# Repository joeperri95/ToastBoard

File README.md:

# ToastBoard

Why use a breadboard when all your I/O is right here?

## Features

* 4 LEDs
* 4 Push buttons
* Quad DIP switch
* 2 Potentiometers
* I2C EEPROM
* I2C temperature sensor

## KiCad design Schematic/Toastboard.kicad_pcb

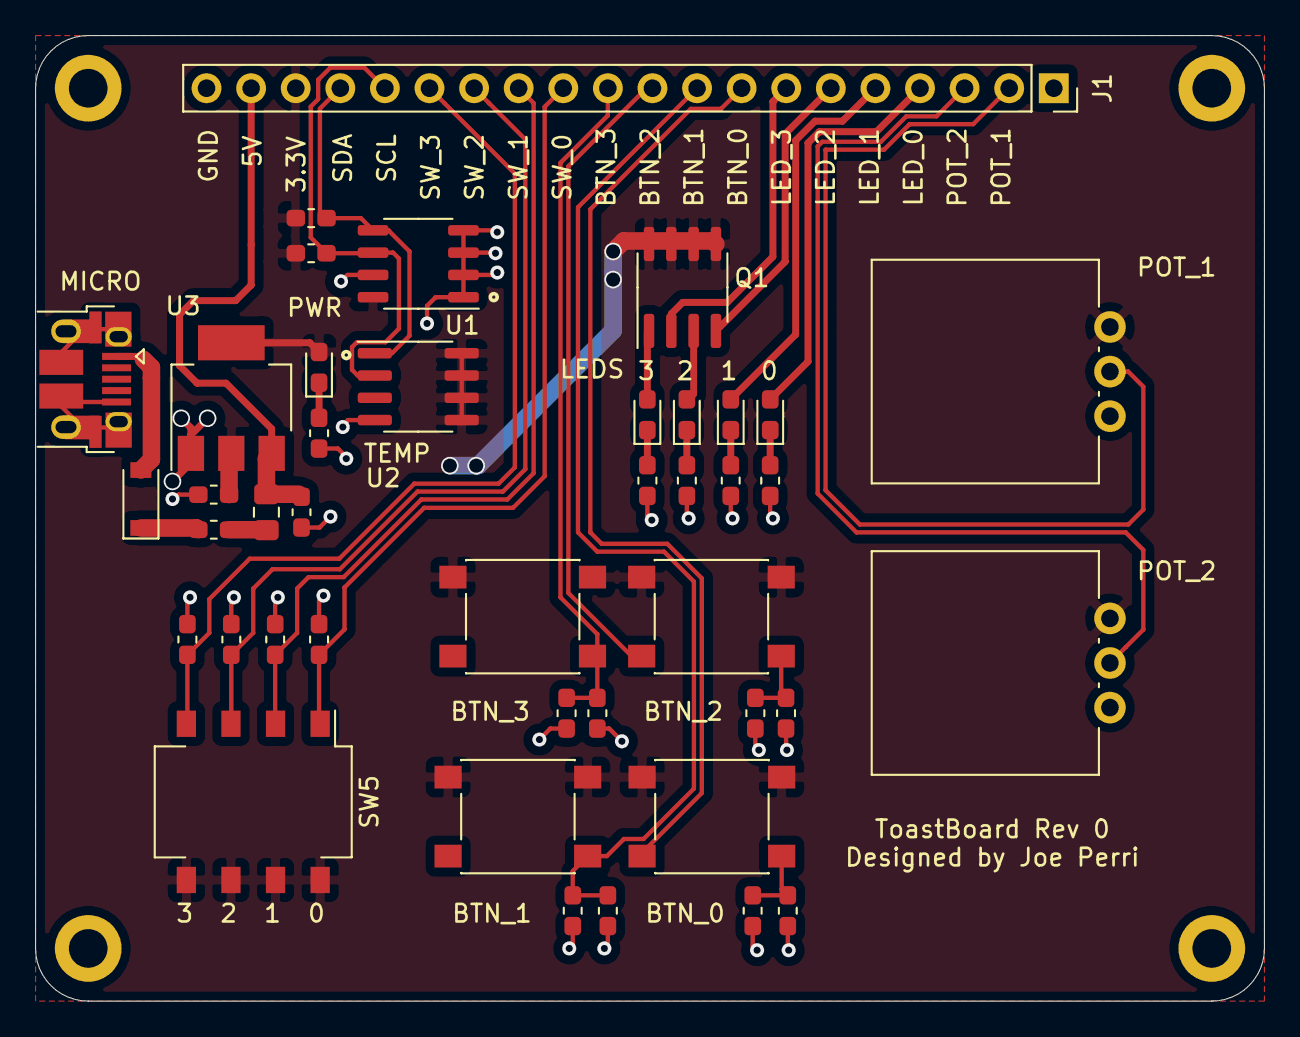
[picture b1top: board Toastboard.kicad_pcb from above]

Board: 2 copper layers, 70.0 x 55.0 mm, 46 parts (0 on the bottom side), 29 nets.

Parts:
BTN_0, BTN_1, BTN_2, BTN_3: SW_Push; SW_Push_1P1T_NO_6x6mm_H9.5mm
C1, C2: 10u; C_0603_1608Metric_Pad1.05x0.95mm_HandSolder
C3, C4, C5, C6: 100n; C_0603_1608Metric_Pad1.05x0.95mm_HandSolder
D1, D3, D4, D5, D6: LED; LED_0603_1608Metric_Pad1.05x0.95mm_HandSolder
D2: D_Schottky; D_SOD-123
F1: 1A; Fuse_0603_1608Metric_Pad1.05x0.95mm_HandSolder
FB1: Ferrite_Bead; L_0805_2012Metric_Pad1.15x1.40mm_HandSolder
H1, H2, H3, H4: Pad; MountingHole_2.2mm_M2_DIN965_Pad
J1: Conn_01x20_Female; PinSocket_1x20_P2.54mm_Vertical
MICRO: USB_B_Micro; USB_Micro-B_Amphenol_10103594-0001LF_Horizontal
Q1: FDS6892A; SOIC-8_3.9x4.9mm_P1.27mm
R1, R2, R3, R4, R7: 220; R_0603_1608Metric_Pad1.05x0.95mm_HandSolder
R5, R6, R8, R9, R10, R14: 10k; R_0603_1608Metric_Pad1.05x0.95mm_HandSolder
R11, R12, R13, R15: 10K; R_0603_1608Metric_Pad1.05x0.95mm_HandSolder
RV1, RV2: R_POT; Potentiometer_Vishay_248GJ-249GJ_Single_Vertical
SW5: SW_DIP_x04; SW_DIP_SPSTx04_Slide_Omron_A6S-410x_W8.9mm_P2.54mm
U1: 24LC01; SO-8_3.9x4.9mm_P1.27mm
U2: LM75B; SOIC-8_3.9x4.9mm_P1.27mm
U3: AMS1117-3.3; SOT-223-3_TabPin2

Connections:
+3V3: BTN_0.1, BTN_1.1, BTN_2.1, BTN_3.1, C2.1, D6.2, J1.18, Q1.5, Q1.6, Q1.7, Q1.8, R5.1, R6.1, RV1.1, RV2.1, SW5.5, SW5.6, SW5.7, SW5.8, U1.8, U2.5, U2.6, U2.7, U2.8, U3.2
+5V: C1.1, FB1.1, J1.19, U3.3
/BTN_0: BTN_0.2, C3.1, J1.8, R8.1
/BTN_1: BTN_1.2, C4.1, J1.9, R9.1
/BTN_2: BTN_2.2, C5.1, J1.10, R10.1
/BTN_3: BTN_3.2, C6.1, J1.11, R14.1
/LED_0: D5.2, J1.4
/LED_1: D4.2, J1.5
/LED_2: J1.6, Q1.4
/LED_3: J1.7, Q1.2
/POT_1: J1.2, RV1.2
/POT_2: J1.3, RV2.2
/SCL: J1.16, R5.2, U1.6, U2.2
/SDA: J1.17, R6.2, U1.5, U2.1
/SW_0: J1.12, R11.1, SW5.1
/SW_1: J1.13, R12.1, SW5.2
/SW_2: J1.14, R13.1, SW5.3
/SW_3: J1.15, R15.1, SW5.4
GND: C1.2, C2.2, C3.2, C4.2, C5.2, C6.2, H1.1, H2.1, H3.1, H4.1, J1.1, J1.20, MICRO.5, MICRO.6, R1.2, R2.2, R3.2, R4.2, R7.2, R8.2, R9.2, R10.2, R11.2, R12.2, R13.2, R14.2, R15.2, RV1.3, RV2.3, U1.1, U1.2, U1.3, U1.4, U1.7, U2.4, U3.1
unnamed: D1.1, R1.1
unnamed: D1.2, Q1.1
unnamed: D2.1, F1.2
unnamed: D2.2, MICRO.1
unnamed: D3.1, R2.1
unnamed: D3.2, Q1.3
unnamed: D4.1, R3.1
unnamed: D5.1, R4.1
unnamed: D6.1, R7.1
unnamed: F1.1, FB1.2

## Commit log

2020-06-23 Add initial schematic
2020-06-23 Add values to schematic
2020-06-23 Initial placement
2020-06-24 Layout
2020-06-24 Increased via size. Added JLC tracking number
2020-06-24 Change footprints to match available parts
